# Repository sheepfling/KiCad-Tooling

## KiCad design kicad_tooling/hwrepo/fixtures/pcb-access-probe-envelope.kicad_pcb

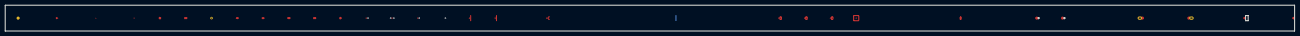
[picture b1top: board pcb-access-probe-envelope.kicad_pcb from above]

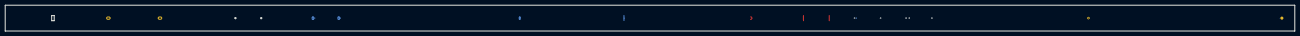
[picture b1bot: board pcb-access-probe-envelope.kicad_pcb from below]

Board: 2 copper layers, 500.0 x 10.0 mm, 46 parts (6 on the bottom side), 3 nets.

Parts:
H1: NPTH Boundary; MountingHole
H2: NPTH One Nanometer Inside; MountingHole
H3: Plated Oblong Boundary; SlottedPlatedHole
H4: Plated Oblong One Nanometer Inside; SlottedPlatedHole
J1: AccessTarget
J2: SameNetNeighbor; AccessNeighbor
J3: DnpNeighbor; AccessNeighbor
J4: FrontObstacle; AccessNeighbor
J5: BackObstacle; AccessNeighbor
J7: NoNetNeighborTarget; AccessTarget
J8: UnconnectedObstacle; AccessNeighbor
J9: FrontOnlyTarget; AccessTarget
J10: FrontOnlyObstacle; AccessNeighbor
J11: UndersizeApertureFault; AccessTarget
J12: ExactApertureBoundaryControl; AccessTarget
J13: RectangularApertureBoundaryControl; AccessTarget
J14: DrilledApertureUnsupported; AccessTarget
J15: UndersizeOvalApertureFault; AccessTarget
J16: ExactOvalApertureBoundaryControl; AccessTarget
J17: UndersizeRoundrectApertureFault; AccessTarget
J18: ExactRoundrectApertureBoundaryControl; AccessTarget
J19: CourtyardClearanceFault; AccessTarget
J20: UntentedViaClearanceFault; AccessTarget
J21: UntentedViaBoundaryControl; AccessTarget
J22: TentedViaControl; AccessTarget
J23: BackUntentedViaFault; AccessTarget
J24: TrackClearanceFault; AccessTarget
J25: TrackClearanceBoundaryControl; AccessTarget
J26: SameNetTrackControl; AccessTarget
J27: UnconnectedTrackArcFault; AccessTarget
J28: ForeignZoneClearanceFault; AccessTarget
J29: ForeignZoneBoundaryControl; AccessTarget
J30: SameNetZoneControl; AccessTarget
J31: FilledZoneHoleControl; AccessTarget
J32: BackZoneClearanceFault; AccessTarget
J33: BackZoneClearanceBoundaryControl; AccessTarget
J34: BoardEdgeBoundaryControl; AccessTarget
J35: BoardEdgeClearanceFault; AccessTarget
J36: DrillHoleBoundaryControl; AccessTarget
J37: DrillHoleClearanceFault; AccessTarget
J38: OblongDrillBoundaryControl; AccessTarget
J39: OblongDrillClearanceFault; AccessTarget
U1: CourtyardBoundaryControl; AccessBody
U2: CourtyardClearanceFault; AccessBody
U3: OppositeSideCourtyardControl; AccessBody
U4: DnpCourtyardControl; AccessBody

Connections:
TARGET_ACCESS: J1.1, J2.1
TARGET_OBLONG_HOLE_BOUNDARY: H3.1, J38.1
TARGET_OBLONG_HOLE_FAULT: H4.1, J39.1
